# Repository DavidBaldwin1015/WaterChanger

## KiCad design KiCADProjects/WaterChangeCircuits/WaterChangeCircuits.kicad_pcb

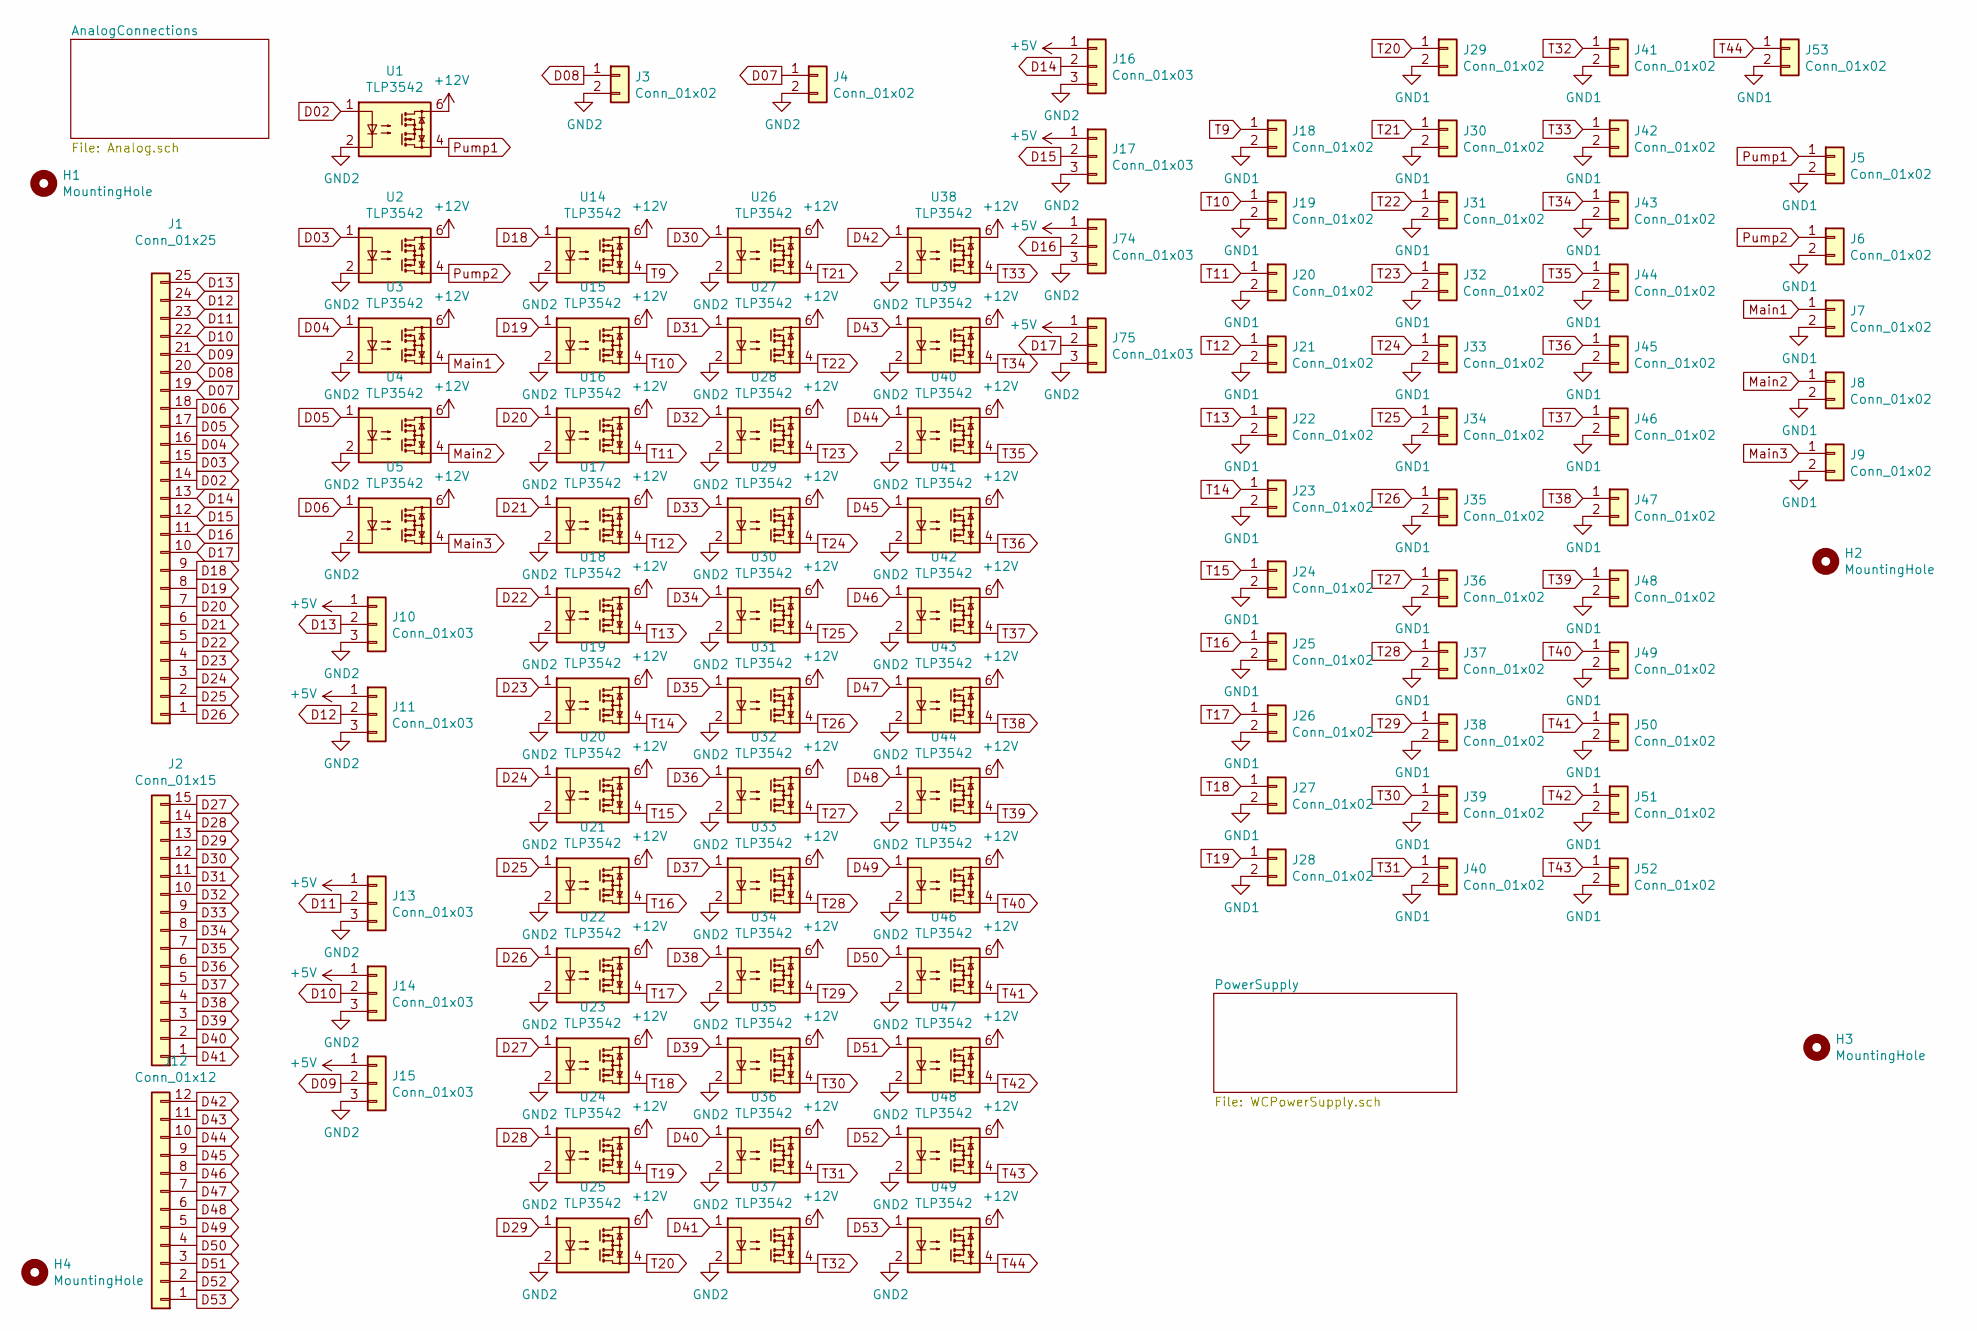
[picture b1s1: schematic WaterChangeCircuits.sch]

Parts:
H1, H2, H3, H4: MountingHole; MountingHole_3.2mm_M3
J1: Conn_01x25; PinSocket_1x25_P2.54mm_Vertical
J2: Conn_01x15; PinSocket_1x15_P2.54mm_Vertical
J3, J4, J5, J6, J7, J8, J9, J18, J19, J20, J21, J22, J23, J24, J25, J26, J27, J28, J29, J30, J31, J32, J33, J34, J35, J36, J37, J38, J39, J40, J41, J42, J43, J44, J45, J46, J47, J48, J49, J50, J51, J52, J53: Conn_01x02; JST_PH_S2B-PH-K_1x02_P2.00mm_Horizontal
J10, J11, J13, J14, J15, J16, J17, J74, J75: Conn_01x03; PinSocket_1x03_P2.54mm_Vertical
J12: Conn_01x12; PinSocket_1x12_P2.54mm_Vertical
U1, U2, U3, U4, U5, U14, U15, U16, U17, U18, U19, U20, U21, U22, U23, U24, U25, U26, U27, U28, U29, U30, U31, U32, U33, U34, U35, U36, U37, U38, U39, U40, U41, U42, U43, U44, U45, U46, U47, U48, U49: TLP3542; DIP-5-6_W7.62mm

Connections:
+5V: J10.1, J11.1, J13.1, J14.1, J15.1, J16.1, J17.1, J74.1, J75.1; also elsewhere on the board
+12V: U1.6, U2.6, U3.6, U4.6, U5.6, U14.6, U15.6, U16.6, U17.6, U18.6, U19.6, U20.6, U21.6, U22.6, U23.6, U24.6, U25.6, U26.6, U27.6, U28.6, U29.6, U30.6, U31.6, U32.6, U33.6, U34.6, U35.6, U36.6, U37.6, U38.6, U39.6, U40.6, U41.6, U42.6, U43.6, U44.6, U45.6, U46.6, U47.6, U48.6, U49.6; also elsewhere on the board
D02: J1.14, U1.1
D03: J1.15, U2.1
D04: J1.16, U3.1
D05: J1.17, U4.1
D06: J1.18, U5.1
D07: J1.19, J4.1
D08: J1.20, J3.1
D09: J1.21, J15.2
D10: J1.22, J14.2
D11: J1.23, J13.2
D12: J1.24, J11.2
D13: J1.25, J10.2
D14: J1.13, J16.2
D15: J1.12, J17.2
D16: J1.11, J74.2
D17: J1.10, J75.2
D18: J1.9, U14.1
D19: J1.8, U15.1
D20: J1.7, U16.1
D21: J1.6, U17.1
D22: J1.5, U18.1
D23: J1.4, U19.1
D24: J1.3, U20.1
D25: J1.2, U21.1
D26: J1.1, U22.1
D27: J2.15, U23.1
D28: J2.14, U24.1
D29: J2.13, U25.1
D30: J2.12, U26.1
D31: J2.11, U27.1
D32: J2.10, U28.1
D33: J2.9, U29.1
D34: J2.8, U30.1
D35: J2.7, U31.1
D36: J2.6, U32.1
D37: J2.5, U33.1
D38: J2.4, U34.1
D39: J2.3, U35.1
D40: J2.2, U36.1
D41: J2.1, U37.1
D42: J12.12, U38.1
D43: J12.11, U39.1
D44: J12.10, U40.1
D45: J12.9, U41.1
D46: J12.8, U42.1
D47: J12.7, U43.1
D48: J12.6, U44.1
D49: J12.5, U45.1
D50: J12.4, U46.1
D51: J12.3, U47.1
D52: J12.2, U48.1
D53: J12.1, U49.1
GND1: J5.2, J6.2, J7.2, J8.2, J9.2, J18.2, J19.2, J20.2, J21.2, J22.2, J23.2, J24.2, J25.2, J26.2, J27.2, J28.2, J29.2, J30.2, J31.2, J32.2, J33.2, J34.2, J35.2, J36.2, J37.2, J38.2, J39.2, J40.2, J41.2, J42.2, J43.2, J44.2, J45.2, J46.2, J47.2, J48.2, J49.2, J50.2, J51.2, J52.2, J53.2; also elsewhere on the board
GND2: J3.2, J4.2, J10.3, J11.3, J13.3, J14.3, J15.3, J16.3, J17.3, J74.3, J75.3, U1.2, U2.2, U3.2, U4.2, U5.2, U14.2, U15.2, U16.2, U17.2, U18.2, U19.2, U20.2, U21.2, U22.2, U23.2, U24.2, U25.2, U26.2, U27.2, U28.2, U29.2, U30.2, U31.2, U32.2, U33.2, U34.2, U35.2, U36.2, U37.2, U38.2, U39.2, U40.2, U41.2, U42.2, U43.2, U44.2, U45.2, U46.2, U47.2, U48.2, U49.2; also elsewhere on the board
Main1: J7.1, U3.4
Main2: J8.1, U4.4
Main3: J9.1, U5.4
Pump1: J5.1, U1.4
Pump2: J6.1, U2.4
T9: J18.1, U14.4
T10: J19.1, U15.4
T11: J20.1, U16.4
T12: J21.1, U17.4
T13: J22.1, U18.4
T14: J23.1, U19.4
T15: J24.1, U20.4
T16: J25.1, U21.4
T17: J26.1, U22.4
T18: J27.1, U23.4
T19: J28.1, U24.4
T20: J29.1, U25.4
T21: J30.1, U26.4
T22: J31.1, U27.4
T23: J32.1, U28.4
T24: J33.1, U29.4
T25: J34.1, U30.4
T26: J35.1, U31.4
T27: J36.1, U32.4
T28: J37.1, U33.4
T29: J38.1, U34.4
T30: J39.1, U35.4
T31: J40.1, U36.4
T32: J41.1, U37.4
T33: J42.1, U38.4
T34: J43.1, U39.4
T35: J44.1, U40.4
T36: J45.1, U41.4
T37: J46.1, U42.4
T38: J47.1, U43.4
T39: J48.1, U44.4
T40: J49.1, U45.4
T41: J50.1, U46.4
T42: J51.1, U47.4
T43: J52.1, U48.4
T44: J53.1, U49.4

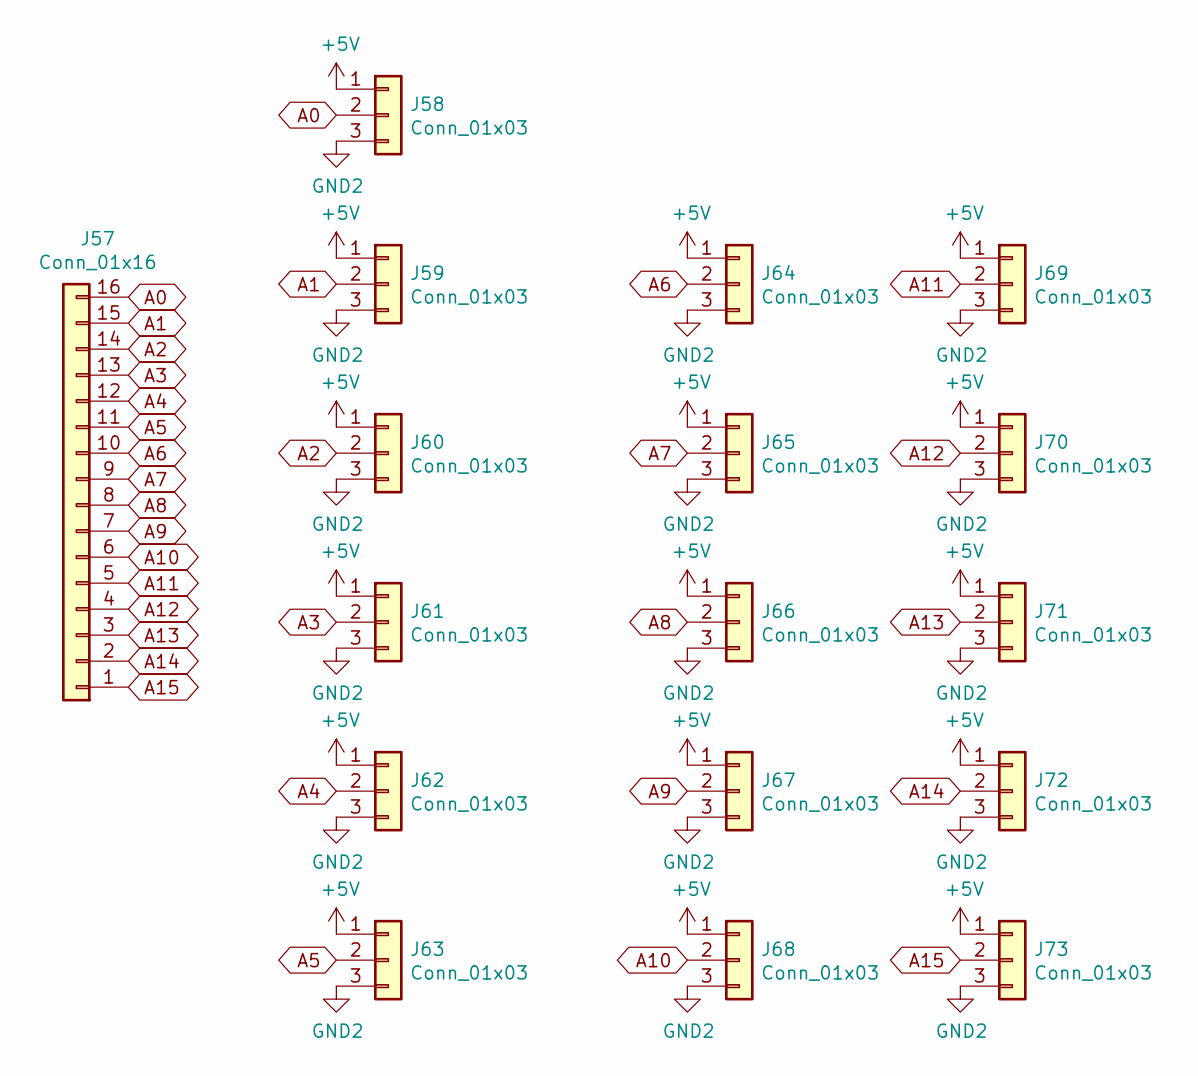
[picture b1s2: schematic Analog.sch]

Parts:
J57: Conn_01x16; PinSocket_1x16_P2.54mm_Vertical
J58, J59, J60, J61, J62, J63, J64, J65, J66, J67, J68, J69, J70, J71, J72, J73: Conn_01x03; PinSocket_1x03_P2.54mm_Vertical

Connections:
+5V: J58.1, J59.1, J60.1, J61.1, J62.1, J63.1, J64.1, J65.1, J66.1, J67.1, J68.1, J69.1, J70.1, J71.1, J72.1, J73.1; also elsewhere on the board
A0: J57.16, J58.2
A1: J57.15, J59.2
A2: J57.14, J60.2
A3: J57.13, J61.2
A4: J57.12, J62.2
A5: J57.11, J63.2
A6: J57.10, J64.2
A7: J57.9, J65.2
A8: J57.8, J66.2
A9: J57.7, J67.2
A10: J57.6, J68.2
A11: J57.5, J69.2
A12: J57.4, J70.2
A13: J57.3, J71.2
A14: J57.2, J72.2
A15: J57.1, J73.2
GND2: J58.3, J59.3, J60.3, J61.3, J62.3, J63.3, J64.3, J65.3, J66.3, J67.3, J68.3, J69.3, J70.3, J71.3, J72.3, J73.3; also elsewhere on the board

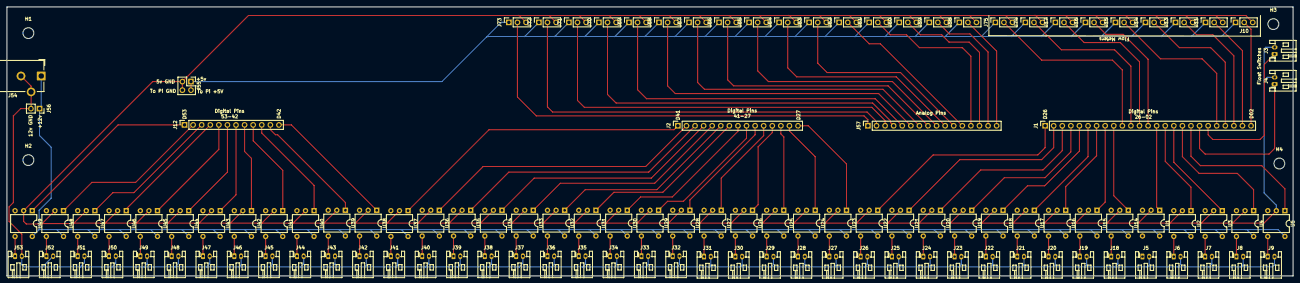
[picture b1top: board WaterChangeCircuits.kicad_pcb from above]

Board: 2 copper layers, 380.7 x 79.6 mm, 120 parts (0 on the bottom side), 113 nets.

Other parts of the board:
J54: Barrel_Jack_Switch; BarrelJack_CUI_PJ-102AH_Horizontal
J55: Conn_02x02_Odd_Even; PinHeader_2x02_P2.54mm_Vertical
J56: Conn_01x02; PinSocket_1x02_P2.54mm_Vertical

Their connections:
+5V: J55.1, J55.2; also elsewhere on the board
+12V: J54.1, J56.1; also elsewhere on the board
GND1: J54.2, J54.3, J56.2; also elsewhere on the board
GND2: J55.3, J55.4; also elsewhere on the board

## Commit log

2021-05-23 Ading all dev files
2021-05-24 Updated circuits, added code from Adafruit for the flow meter, added some more commands to the main file
2021-05-24 Cleaned up some files that were in the wrong place, or no longer needed
2021-05-25 Changed the circuit design to make the inputs from the flowmeters digital, started the webform designs for the RPi
2021-05-26 Completed PCB design and schematics.
2021-05-26 Added PDF of the PCB layout
2021-05-26 Added PDF of the schematic
2021-06-02 Updated some design files and added parts of the web app
2021-06-02 Updated the web app
2021-06-02 Update to the web app
2021-06-02 typo
2021-06-02 fixed the php script for adding devices
2021-06-02 Updated data handling
2021-06-03 Added on to the web app, fixed the add device form, added styling
2021-06-03 Fixed a few typos
2021-06-03 Cleaned up the code to prevent repeat responses
2021-06-03 Attempting to fix the error in adding a device
2021-06-03 More corrections
2021-06-03 New error checking for adding database records
2021-06-03 New method for adding records
2021-06-03 Fixed null variable error when attempting to add new records
2021-06-04 Added a query to the new device script, added a csv file of all the pins for the DB
2021-06-04 removed an unnecessary index file
2021-06-04 Fixed some issues with the New Device script
2021-06-04 Edited some styling stuff
2021-06-05 Completed the pump control page, added a lot of functions to the arduino code, added error alert code to the dashboard.
2021-06-05 Fixed typos
2021-06-05 Added commands to close php to mysql connections
2021-06-05 Fixed some errors
2021-06-05 Added a python script for passing serial commands to Arduino
2021-06-06 Attempt to fix an error
2021-06-07 Fixed the rror in the python serial control script
2021-06-07 finally fixed the python serial script, apparently the Arduino was resetting whenever a serial connection was made
2021-06-07 Fixed an error where commands were repeated
2021-06-07 Added some commands for the pumps, updated the logic in the Arduino firmware
2021-06-07 Fixed a SQL error
2021-06-07 Fixed a JS error
2021-06-07 Added a PHP script to check settings
2021-06-07 Fixed some PHP errors
2021-06-08 Started adding a flowmeter function and functions for digital pin reads
